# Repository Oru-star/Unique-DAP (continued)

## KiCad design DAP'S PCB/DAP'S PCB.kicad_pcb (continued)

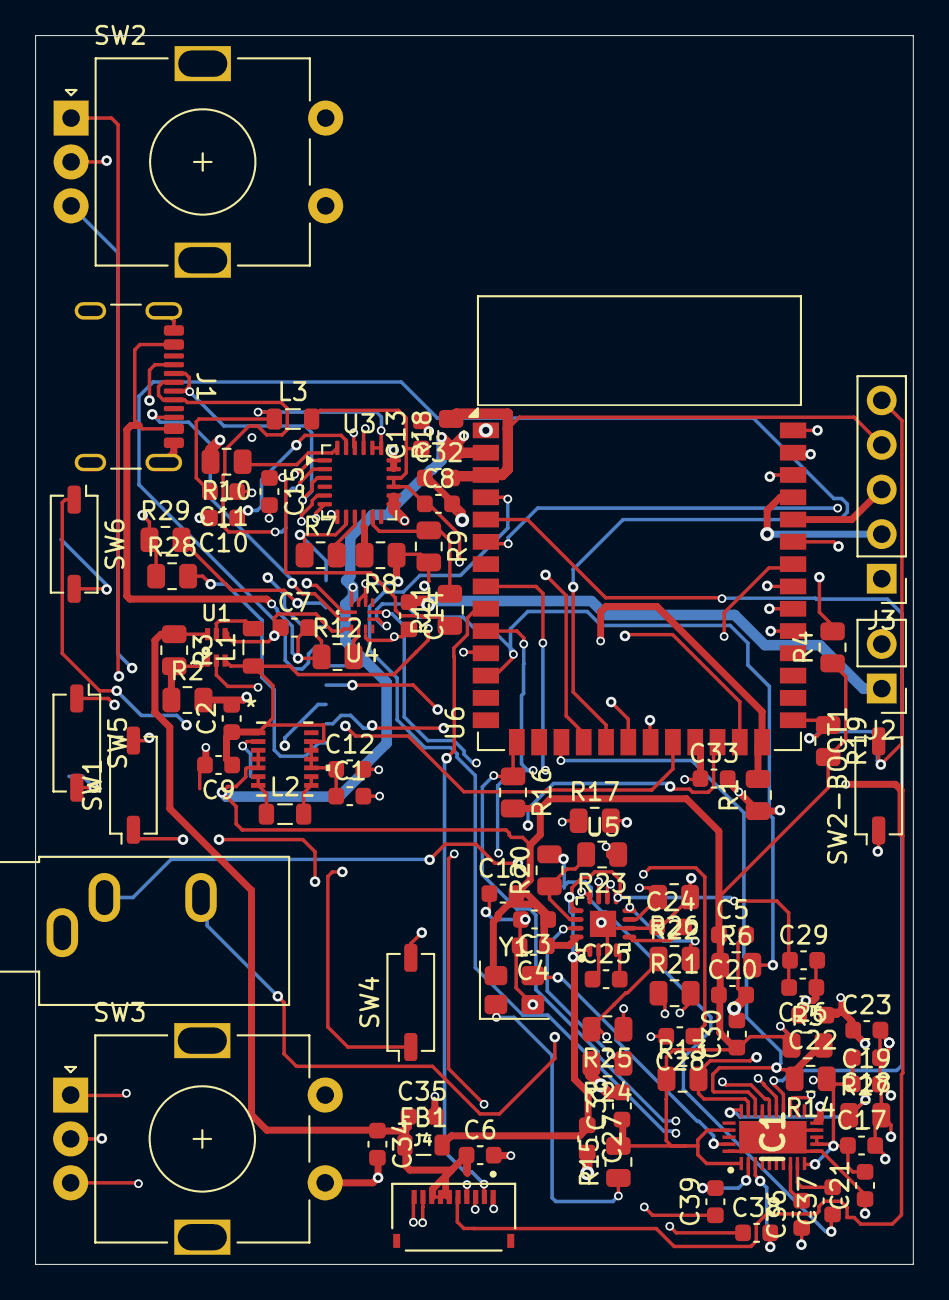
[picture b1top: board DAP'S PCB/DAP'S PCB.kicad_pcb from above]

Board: 4 copper layers, 50.0 x 70.0 mm, 93 parts (1 on the bottom side), 78 nets.

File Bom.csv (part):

Category,RefDes,Qty,Item / value,Manufacturer,MPN / candidate,PCB footprint / package,Supplier,Unit price (INR),Extended (INR),Stock / price basis,Status,Source URL,Engineering / procurement notes
Display,DISP1,1,"3.16-in reflective memory LCD, 336 × 536, serial interface",Sharp,LS032B7DD02,External module; mates to J4 FPC,DigiKey India,3739.83,3739.83,388 listed; verify live stock and long standard lead time,BUY,https://www.digikey.in/en/products/detail/sharp-microelectro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,"5 V module supply; 3 V serial logic. Verify display FPC orientation, flex dimensions and pin mapping against Sharp datasheet before ordering."
DAC,IC1,1,32-bit stereo audio DAC,ESS / formerly ESS Technology,ES9038Q2M,QFN-40; project footprint ES9038Q2M:QFN40P300X500X80-31N-D,Mouser India,1967.96,1967.96,"3,163 listed at capture; verify live",BUY,https://www.mouser.in/c/?q=ES9038Q2M,Confirm exact package/land pattern and analog/digital rail implementation against ESS datasheet.
Power IC,U1,1,3.7-A boost converter,Texas Instruments,TPS61023DRLR,SOT-563-6; project footprint TPS61023DRLR:SOT563-ORI,Mouser India,116.56,116.56,"4,524 listed at capture; verify live",BUY,https://www.mouser.in/c/?q=TPS61023DRLR,L1 must be redesigned for a power inductor; do not fit an 0805 signal inductor.
Power IC,U2,1,Buck-boost converter,Texas Instruments,TPS63021DSJR,DSJ 14-pin 2.85 × 1.58 mm,Mouser India,311.22,311.22,"1,025 listed at capture; verify live",BUY,https://www.mouser.in/c/?q=TPS63021DSJR,Requires a suitable 1.5 µH power inductor; current 0805 footprint is not acceptable.
Charger IC,U3,1,1-cell Li-ion/Li-poly charger with power-path management,Texas Instruments,BQ25895RTWR,24-pin WQFN 4 × 4 mm with exposed pad,DigiKey India,321.05,321.05,"3,384 listed at capture; verify live",VERIFY,https://www.digikey.in/en/products/result?keywords=BQ25895RTWR,"Verify TS network, programmed charge current and thermal layout. L3 selection depends on charge-current and ripple setting."
USB-C controller,U4,1,USB Type-C configuration channel controller,Texas Instruments,TUSB320LAIRWBR,RWB0012A 12-pin X2QFN 1.6 × 1.6 mm,DigiKey India,174.05,174.05,"10,882 listed at capture; verify live",BUY,https://www.digikey.in/en/products/result?keywords=TUSB320LAIRWBR,Footprint pad dimensions were adjusted during DRC cleanup; re-check against TI land pattern before fabrication.
Headphone amplifier,U5,1,Stereo DirectDrive headphone amplifier,Analog Devices / Maxim,MAX97220AETE+T,TQFN/QFN-16 3 × 3 mm; exposed pad,Mouser India,231.09,231.09,"2,381 listed at capture; verify live",BUY,https://www.mouser.in/c/?q=MAX97220AETE%2BT,J5 headphone jack is wired to OUTL/OUTR and audio ground; validate output network and layout from datasheet.
MCU module,U6,1,ESP32-S3 Wi-Fi/Bluetooth module; candidate 8 MB flash + 8 MB PSRAM,Espressif,ESP32-S3-WROOM-1-N8R8 (verify suffix),RF_Module:ESP32-S3-WROOM-1,Mouser India,599.99,599.99,"3,317 listed at capture; verify live",VERIFY,https://www.mouser.in/c/?q=ESP32-S3-WROOM-1-N8R8,The PCB value shown in the inventory omits the memory suffix. Confirm firmware target and exact module order code.
USB-C receptacle,J1,1,USB 2.0 Type-C top-mount receptacle,GCT,USB4105-GF-A (candidate),Connector_USB:USB_C_Receptacle_GCT_USB4105-xx-A_16P_TopMnt_Horizontal,DigiKey India,76.44,76.44,"140,000+ listed at capture; verify live",VERIFY,https://www.digikey.in/en/products/result?keywords=USB4105-GF-A,"Check the exact GCT USB4105 variant, symbol-to-footprint pad mapping, shell tabs and mechanical outline against the manufacturer's drawing; do not rely on the generic family name alone."
Battery header,J2,1,2-position 2.54 mm straight through-hole pin header,Samtec,TSW-102-07-G-S (candidate),Connector_PinHeader_2.54mm:PinHeader_1x02_P2.54mm_Vertical,DigiKey India,20.07,20.07,"52,615 listed at capture; verify live",VERIFY,https://www.digikey.in/en/products/result?keywords=TSW-102-07-G-S,Select matching cable-side housing/contacts and verify battery polarity before order.
Programming header,J3,1,5-position 2.54 mm straight through-hole pin header,Samtec,TSW-105-07-G-S (candidate),Connector_PinHeader_2.54mm:PinHeader_1x05_P2.54mm_Vertical,element14 India,40.66,40.66,840 listed; supplier MOQ 10 per listing,BUY,https://in.element14.com/samtec/tsw-105-07-g-s/pin-header-5p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,Listed unit price is at 10-piece minimum. Confirm header gender and mating cable.
Display FPC connector,J4,1,"10-position 0.5 mm FPC/FFC ZIF connector, right-angle",Hirose,FH34SRJ-10S-0.5SH(50),fpc_screen:HRS_FH34SRJ-10S-0.5SH_50,Mouser India,86.66,86.66,"2,771 listed at capture; verify live",VERIFY,https://www.mouser.in/c/?q=FH34SRJ-10S-0.5SH%2850%29,"Confirm top/bottom contact orientation, 0.30 mm FPC thickness and Sharp panel pinout before buying."
Headphone jack,J5,1,"3.5 mm stereo TRS right-angle through-hole jack, unswitched",Same Sky / CUI Devices,SJ1-3533NG,Connector_Audio:Jack_3.5mm_CUI_SJ1-3533NG_Horizontal,DigiKey India,160.74,160.74,"330,962 listed at capture; verify live",BUY,https://www.digikey.in/en/products/result?keywords=SJ1-3533NG,KiCad footprint uses named S/T/R pads. Verify body position against enclosure side opening.
Ferrite bead,FB1,1,"600 Ω @ 100 MHz ferrite bead, 0805",Murata,BLM21PG601SN1D,Inductor_SMD:L_0805_2012Metric,DigiKey India,11.47,11.47,"12,996 listed at capture; verify live",VERIFY,https://www.digikey.in/en/products/result?keywords=BLM21PG601SN1D,1.4 A current rating listed. Confirm rail DC current and impedance curve are suitable for the analog supply isolation.
Power inductor,L1,1,1.0 µH shielded power inductor; TI-listed candidate,Würth Elektronik,74438357010,Current PCB footprint: Inductor_SMD:L_0805_2012Metric — WRONG SIZE,Mouser India,161.46,161.46,"9,038 listed at capture; verify live",HOLD,https://www.mouser.in/c/?q=74438357010,"Approx. 4.1 × 4.1 mm power inductor, Isat 9.6 A. Must replace 0805 footprint and re-check height/clearance."
Power inductor,L2,1,1.5 µH shielded power inductor; TI-listed candidate,Coilcraft,XFL4020-152ME,Current PCB footprint: Inductor_SMD:L_0805_2012Metric — WRONG SIZE,DigiKey / Mouser (quote),,,Price/stock not captured,HOLD,https://www.digikey.in/en/products/result?keywords=XFL4020-152ME,"4 × 4 mm class, Isat about 5.1 A. Replace 0805 footprint; verify current and DCR against TPS63021 operating point."
Power inductor,L3,1,2.2 µH shielded power inductor,Murata,DFE322512F-2R2M=P2,Current PCB footprint: Inductor_SMD:L_0805_2012Metric — WRONG SIZE; part is 3.2 × 2.5 mm,element14 India,46.82,46.82,"3,390 listed; 18-week manufacturer lead time also shown",HOLD,https://in.element14.com/murata/dfe322512f-2r2m-p2/inductor-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,"2.6 A DC current, 3.4 A saturation. Confirm BQ25895 programmed ICHG + ripple/2 is within rating; change footprint to match part."
Oscillator,Y1,1,"40.000 MHz CMOS oscillator, 3.3 V, 4-pad 3.2 × 2.5 mm",Abracon,ASE-40.000MHZ-L-C-T,Oscillator_SMD:Abracon_ASE-4pin_3.2x2.5mm,DigiKey India,99.37,99.37,811 listed at capture; verify live,VERIFY,https://www.digikey.in/en/products/result?keywords=ASE-40.00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,Check ES9038Q2M XI clocking/divider mode and supported sample-rate targets before freezing 40 MHz.
Capacitor,"C1,C8-C10,C13,C14,C30",7,"10 µF MLCC, 0603; suggested 10 V X5R",Samsung (candidate),CL10A106KP8NNND (candidate),Capacitor_SMD:C_0603_1608Metric,DigiKey / Mouser search,,,Verify current stock and effective capacitance,VERIFY,https://www.digikey.in/en/products/result?keywords=CL10A106KP8NNND,Choose voltage rating per net. Check DC-bias derating at actual rail voltage; do not substitute based on nominal µF alone.
Capacitor,"C2,C16-C21,C23,C28,C31",10,"100 nF MLCC, 0603; suggested 50 V X7R",Murata,GRM188R71H104KA93D (candidate),Capacitor_SMD:C_0603_1608Metric,DigiKey / Mouser search,,,MPN candidate; verify stock,VERIFY,https://www.digikey.in/en/products/result?keywords=GRM188R71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,"Confirm tolerance and voltage are suitable. 100 nF decoupling is generally low risk, but verify exact net."
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
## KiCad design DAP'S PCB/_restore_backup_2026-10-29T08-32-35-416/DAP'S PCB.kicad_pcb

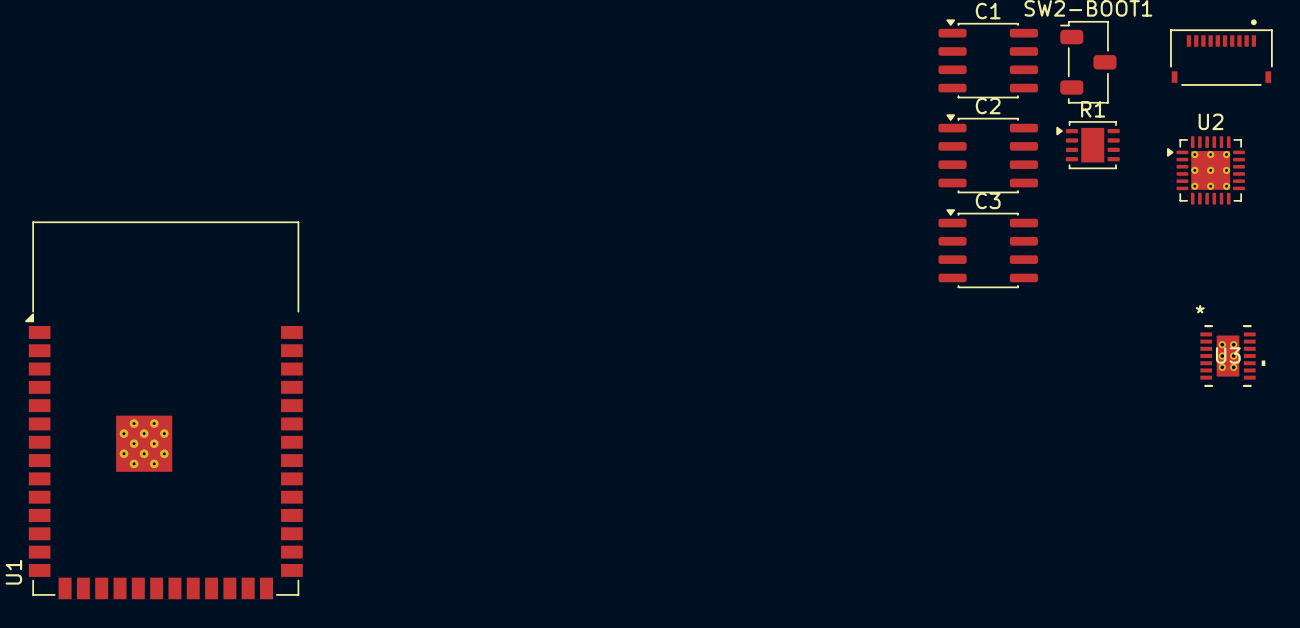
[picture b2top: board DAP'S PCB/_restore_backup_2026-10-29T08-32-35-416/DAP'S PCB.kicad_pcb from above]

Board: 2 copper layers, 9 parts (0 on the bottom side), 15 nets, no tracks yet.

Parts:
C1: 1uF; SOIC-8_3.9x4.9mm_P1.27mm
C2: 10uF; SOIC-8_3.9x4.9mm_P1.27mm
C3: 100nF; SOIC-8_3.9x4.9mm_P1.27mm
J1: SHARP_LS032B7DD02; HRS_FH34SRJ-10S-0.5SH_50_
R1: 10k; HVSON-8-1EP_3x3mm_P0.65mm_EP1.6x2.4mm
SW2-BOOT1: SW_Push; Nidec_Copal_CAS-120A
U1: ESP32-S3-WROOM-1
U2: BQ25895RTW; Texas_RTW_WQFN-24-1EP_4x4mm_P0.5mm_EP2.7x2.7mm_ThermalVias
U3: TPS63021DSJR; DSJ14_2P85X1P58

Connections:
+3V3: C2.1, C3.1, R1.1, U1.2 (3V3)
+5V_LCD: J1.6, J1.7, J1.8
/ESP32S3_Core/EN: C1.2, R1.2, U1.3 (EN)
/ESP32S3_Core/IO0: SW2-BOOT1.2, U1.27 (IO0)
/Power_Management/BAT: U2.13 (BAT), U2.14 (BAT)
/Power_Management/SW: U2.19 (SW), U2.20 (SW)
/Power_Management/SYS: U2.15 (SYS), U2.16 (SYS)
GND: C1.1, C2.2, C3.2, J1.9, J1.10, SW2-BOOT1.1, U1.1 (GND), U1.40 (GND), U1.41 (GND), U2.8 (OTG), U2.9 (~CE), U2.17 (PGND), U2.18 (PGND), U2.25 (PGND)
I2C_SCL: U1.17 (IO9), U2.5 (SCL)
I2C_SDA: U1.12 (IO8), U2.6 (SDA)
LCD_DISP: J1.5, U1.23 (IO21)
LCD_EXTCOMIN: J1.4, U1.11 (IO18)
LCD_SCLK: J1.1, U1.8 (IO15)
LCD_SCS: J1.3, U1.10 (IO17)
LCD_SI: J1.2, U1.9 (IO16)

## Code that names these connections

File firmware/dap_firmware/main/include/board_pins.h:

#pragma once

#include "driver/gpio.h"

// Pin assignments transcribed from the uploaded KiCad schematic (pages 4-6).
// GPIO3 and GPIO45 are ESP32-S3 strapping pins. External resistors must
// establish their boot-time states before the firmware configures them.
// GPIO7 is intentionally NOT used: the ES9038Q2M XI pin is driven by the
// separate external oscillator on the DAC sheet; GPIO7's DAC_MCLK label has
// no matching connection at the DAC.
namespace board {
constexpr gpio_num_t BOOST_EN       = GPIO_NUM_45;
constexpr gpio_num_t DAC_RESET_N    = GPIO_NUM_3;
constexpr gpio_num_t BQ_INT_N       = GPIO_NUM_1;

constexpr gpio_num_t I2C_SDA        = GPIO_NUM_8;
constexpr gpio_num_t I2C_SCL        = GPIO_NUM_9;

constexpr gpio_num_t I2S_BCLK       = GPIO_NUM_4;
constexpr gpio_num_t I2S_LRCK       = GPIO_NUM_5;
constexpr gpio_num_t I2S_DOUT       = GPIO_NUM_6;

constexpr gpio_num_t SD_CS          = GPIO_NUM_10;
constexpr gpio_num_t SD_MOSI        = GPIO_NUM_11;
constexpr gpio_num_t SD_SCLK        = GPIO_NUM_12;
constexpr gpio_num_t SD_MISO        = GPIO_NUM_13;

constexpr gpio_num_t LCD_SCLK       = GPIO_NUM_15;
constexpr gpio_num_t LCD_SI         = GPIO_NUM_16;
constexpr gpio_num_t LCD_SCS        = GPIO_NUM_17;
constexpr gpio_num_t LCD_EXTCOMIN   = GPIO_NUM_18;
constexpr gpio_num_t LCD_DISP       = GPIO_NUM_21;

constexpr gpio_num_t ENC1_A         = GPIO_NUM_38;
constexpr gpio_num_t ENC1_B         = GPIO_NUM_39;
constexpr gpio_num_t ENC1_SW        = GPIO_NUM_40;
constexpr gpio_num_t ENC2_A         = GPIO_NUM_41;
constexpr gpio_num_t ENC2_B         = GPIO_NUM_42;
constexpr gpio_num_t ENC2_SW        = GPIO_NUM_47;

constexpr gpio_num_t BTN_PREV       = GPIO_NUM_2;
constexpr gpio_num_t BTN_NEXT       = GPIO_NUM_14;
constexpr gpio_num_t BTN_PLAY       = GPIO_NUM_48;

constexpr int DAC_I2C_ADDRESS       = 0x48; // ADDR is pulled low by R27 in the schematic.
constexpr int LCD_WIDTH             = 336;
constexpr int LCD_HEIGHT            = 536;
constexpr int LCD_ROW_BYTES         = LCD_WIDTH / 8;
constexpr int LCD_FRAME_BYTES       = LCD_ROW_BYTES * LCD_HEIGHT;
}
